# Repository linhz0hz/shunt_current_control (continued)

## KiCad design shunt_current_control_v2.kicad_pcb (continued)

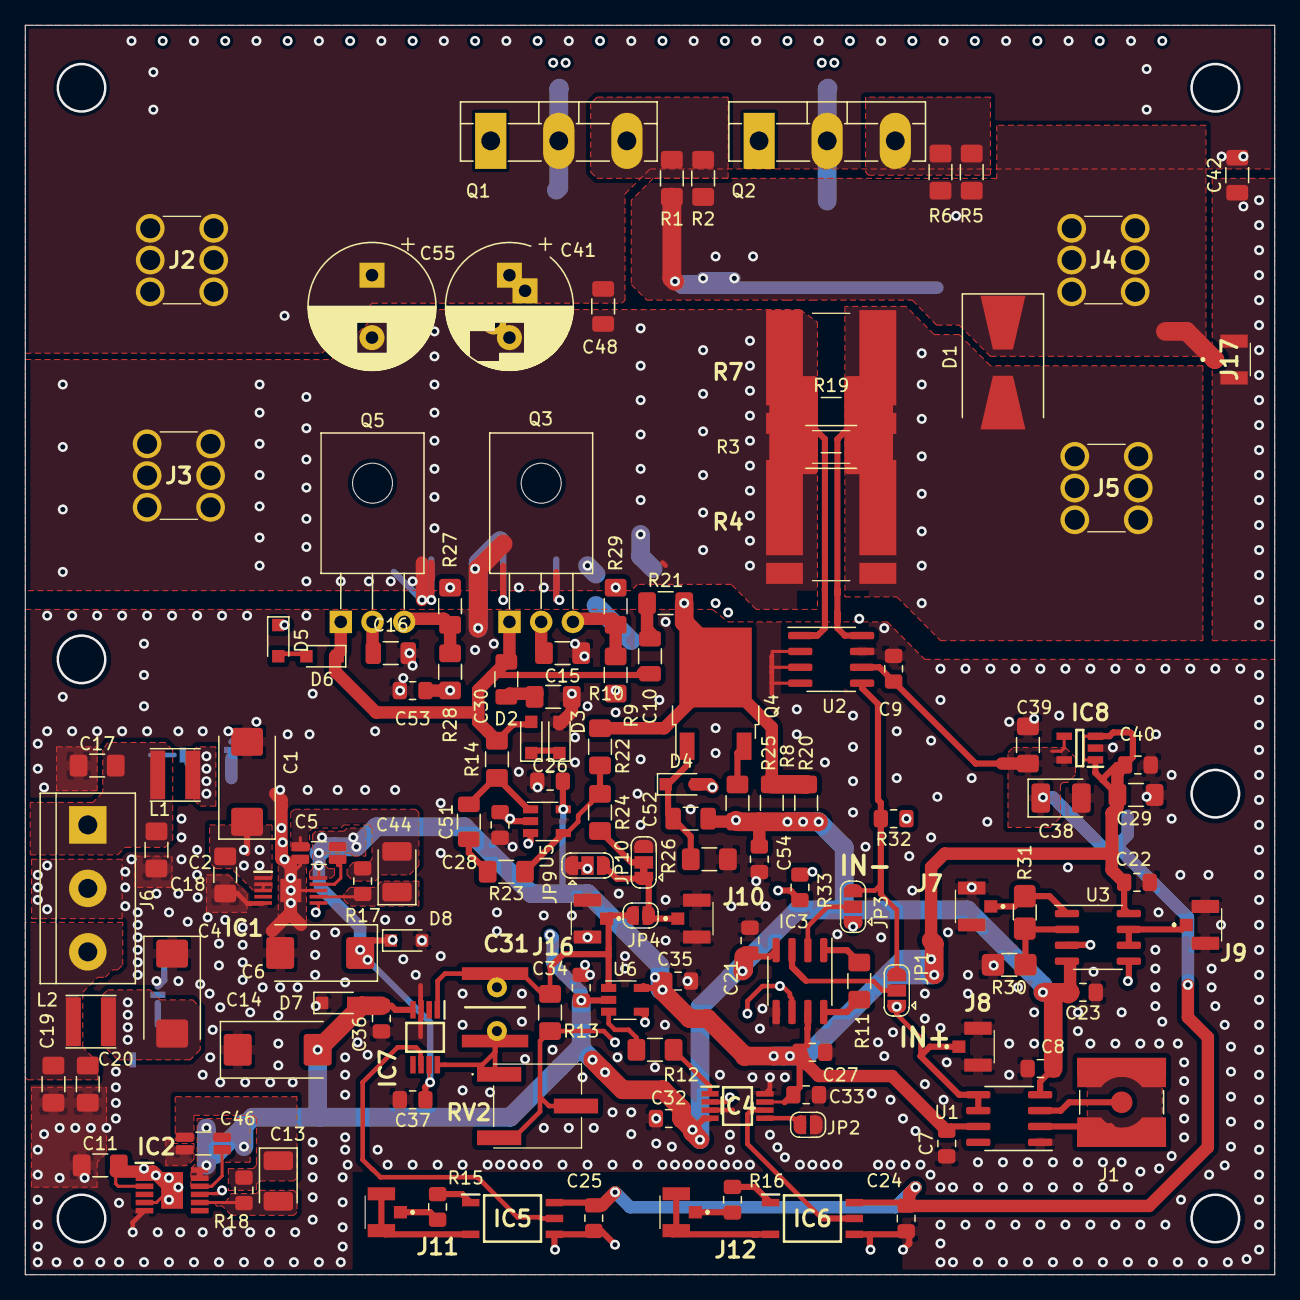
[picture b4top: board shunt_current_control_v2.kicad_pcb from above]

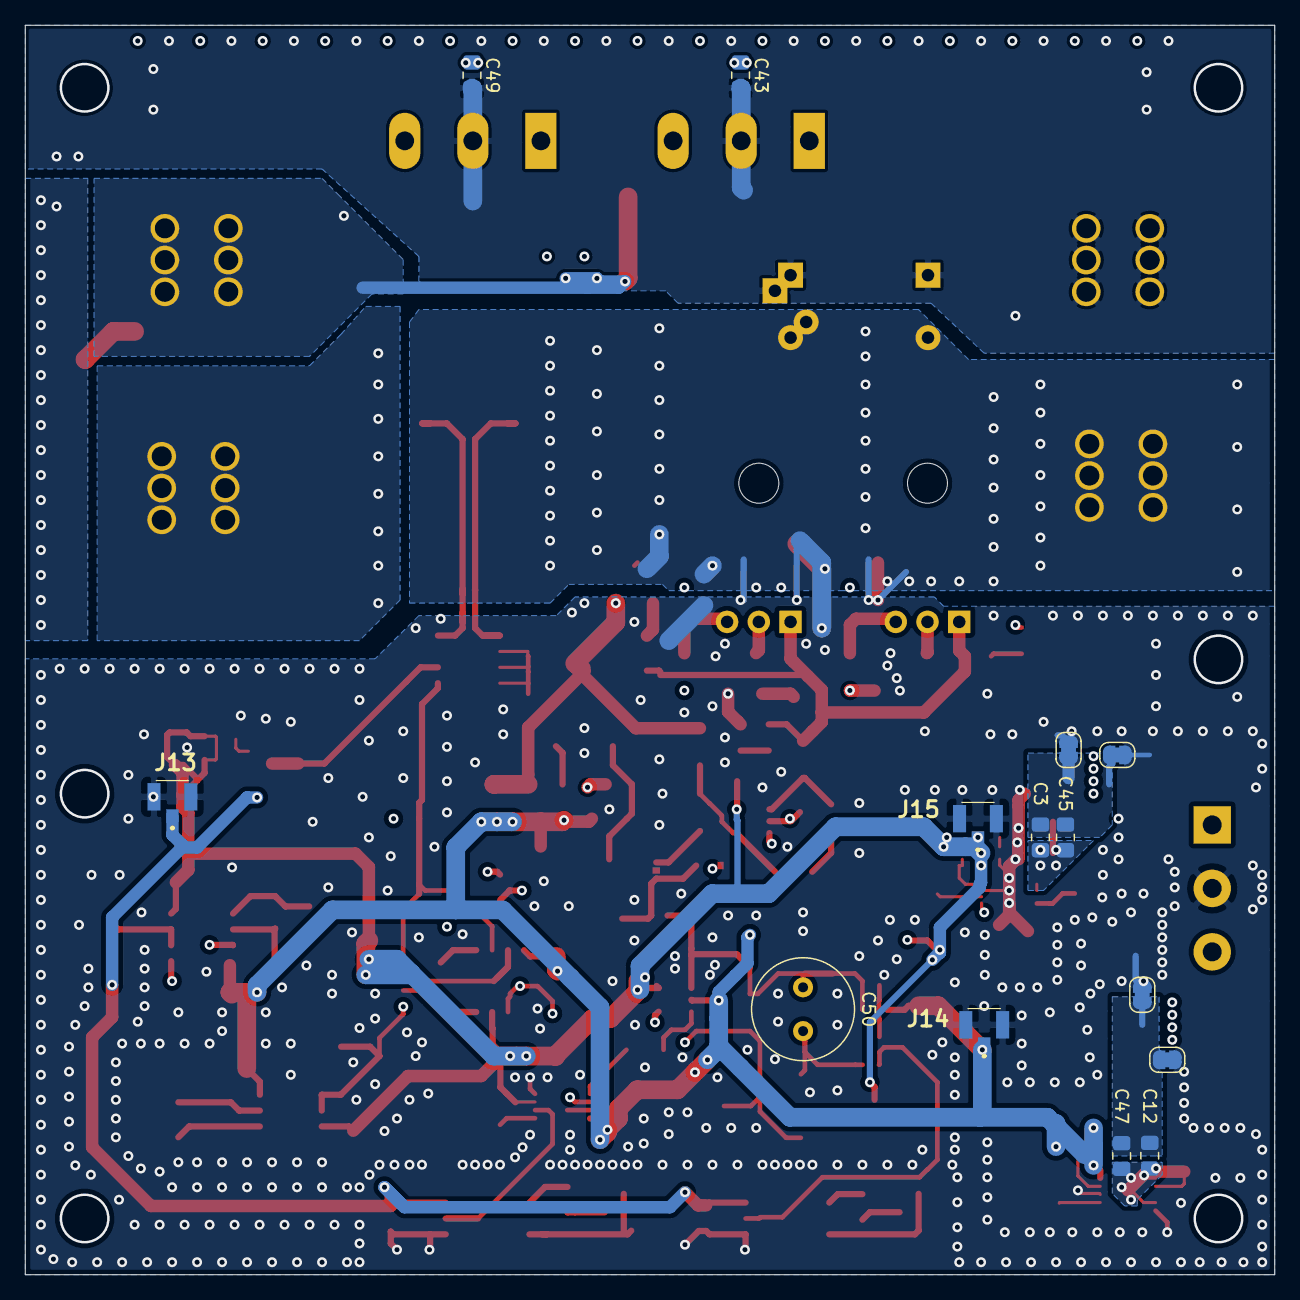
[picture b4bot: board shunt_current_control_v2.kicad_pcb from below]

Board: 4 copper layers, 100.0 x 100.0 mm, 144 parts (14 on the bottom side), 65 nets.

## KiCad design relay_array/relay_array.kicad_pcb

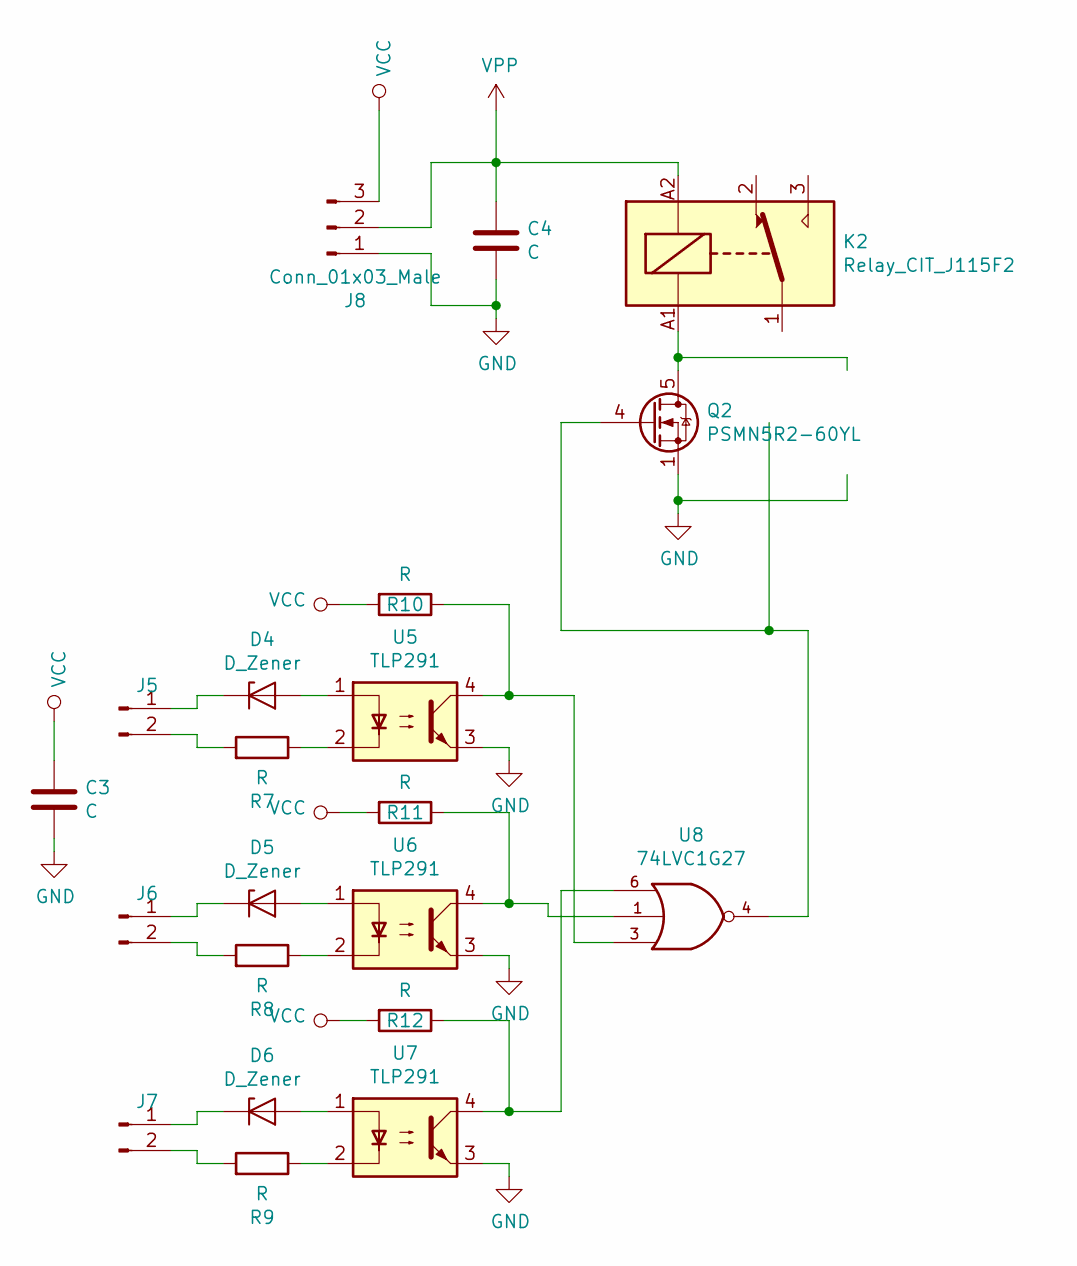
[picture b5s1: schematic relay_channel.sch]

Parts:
C1, C2: C; C_1206_3216Metric_Pad1.42x1.75mm_HandSolder
D1, D2, D3: D_Zener; D_SOD-323_HandSoldering
J1, J2, J3: Conn_01x02_Male; PinHeader_1x02_P2.54mm_Vertical
J4: Conn_01x03_Male; PinHeader_1x03_P2.54mm_Vertical
K1: Relay_CIT_J115F2
Q1: PSMN5R2-60YL; LFPAK56
R1, R2, R3, R4, R5, R6: R; R_0805_2012Metric_Pad1.15x1.40mm_HandSolder
U1, U2, U3: TLP291; SO-4_4.4x3.6mm_P2.54mm
U4: 74LVC1G27; TSOP-6_1.65x3.05mm_P0.95mm

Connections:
GND: C1.2, C2.2, J4.1, Q1.1 (S), Q1.2 (S), Q1.3 (S), U1.3, U2.3, U3.3, U4.2 (GND); also elsewhere on the board
unnamed: D1.1 (K), J1.1
unnamed: D1.2 (A), U1.1
unnamed: D2.1 (K), J2.1
unnamed: D2.2 (A), U2.1
unnamed: D3.1 (K), J3.1
unnamed: D3.2 (A), U3.1
unnamed: J1.2, R1.2
unnamed: J2.2, R2.2
unnamed: J3.2, R3.2
unnamed: K1.A1, Q1.5 (D)
unnamed: Q1.4 (G), U4.4
unnamed: R1.1, U1.2
unnamed: R2.1, U2.2
unnamed: R3.1, U3.2
unnamed: R4.1, U1.4, U4.3
unnamed: R5.1, U2.4, U4.1
unnamed: R6.1, U3.4, U4.6
VCC: C2.1, J4.3, R4.2, R5.2, R6.2, U4.5 (VCC); also elsewhere on the board
VPP: C1.1, J4.2, K1.A2; also elsewhere on the board

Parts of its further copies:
C3, C4, C5, C6: C; C_1206_3216Metric_Pad1.42x1.75mm_HandSolder
D4, D5, D6, D7, D8, D9: D_Zener; D_SOD-323_HandSoldering
J5, J6, J7, J9, J10, J11: Conn_01x02_Male; PinHeader_1x02_P2.54mm_Vertical
J8, J12: Conn_01x03_Male; PinHeader_1x03_P2.54mm_Vertical
K2, K3: Relay_CIT_J115F2
Q2, Q3: PSMN5R2-60YL; LFPAK56
R7, R8, R9, R10, R11, R12, R13, R14, R15, R16, R17, R18: R; R_0805_2012Metric_Pad1.15x1.40mm_HandSolder
U5, U6, U7, U9, U10, U11: TLP291; SO-4_4.4x3.6mm_P2.54mm
U8, U12: 74LVC1G27; TSOP-6_1.65x3.05mm_P0.95mm

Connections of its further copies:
GND: C3.2, C4.2, C5.2, C6.2, J8.1, J12.1, Q2.1 (S), Q2.2 (S), Q2.3 (S), Q3.1 (S), Q3.2 (S), Q3.3 (S), U5.3, U6.3, U7.3, U8.2 (GND), U9.3, U10.3, U11.3, U12.2 (GND); also elsewhere on the board
unnamed: D4.1 (K), J5.1
unnamed: D4.2 (A), U5.1
unnamed: D5.1 (K), J6.1
unnamed: D5.2 (A), U6.1
unnamed: D6.1 (K), J7.1
unnamed: D6.2 (A), U7.1
unnamed: D7.1 (K), J9.1
unnamed: D7.2 (A), U9.1
unnamed: D8.1 (K), J10.1
unnamed: D8.2 (A), U10.1
unnamed: D9.1 (K), J11.1
unnamed: D9.2 (A), U11.1
unnamed: J5.2, R7.2
unnamed: J6.2, R8.2
unnamed: J7.2, R9.2
unnamed: J9.2, R13.2
unnamed: J10.2, R14.2
unnamed: J11.2, R15.2
unnamed: K2.A1, Q2.5 (D)
unnamed: K3.A1, Q3.5 (D)
unnamed: Q2.4 (G), U8.4
unnamed: Q3.4 (G), U12.4
unnamed: R7.1, U5.2
unnamed: R8.1, U6.2
unnamed: R9.1, U7.2
unnamed: R10.1, U5.4, U8.3
unnamed: R11.1, U6.4, U8.1
unnamed: R12.1, U7.4, U8.6
unnamed: R13.1, U9.2
unnamed: R14.1, U10.2
unnamed: R15.1, U11.2
unnamed: R16.1, U9.4, U12.3
unnamed: R17.1, U10.4, U12.1
unnamed: R18.1, U11.4, U12.6
VCC: C3.1, C5.1, J8.3, J12.3, R10.2, R11.2, R12.2, R16.2, R17.2, R18.2, U8.5 (VCC), U12.5 (VCC); also elsewhere on the board
VPP: C4.1, C6.1, J8.2, J12.2, K2.A2, K3.A2; also elsewhere on the board

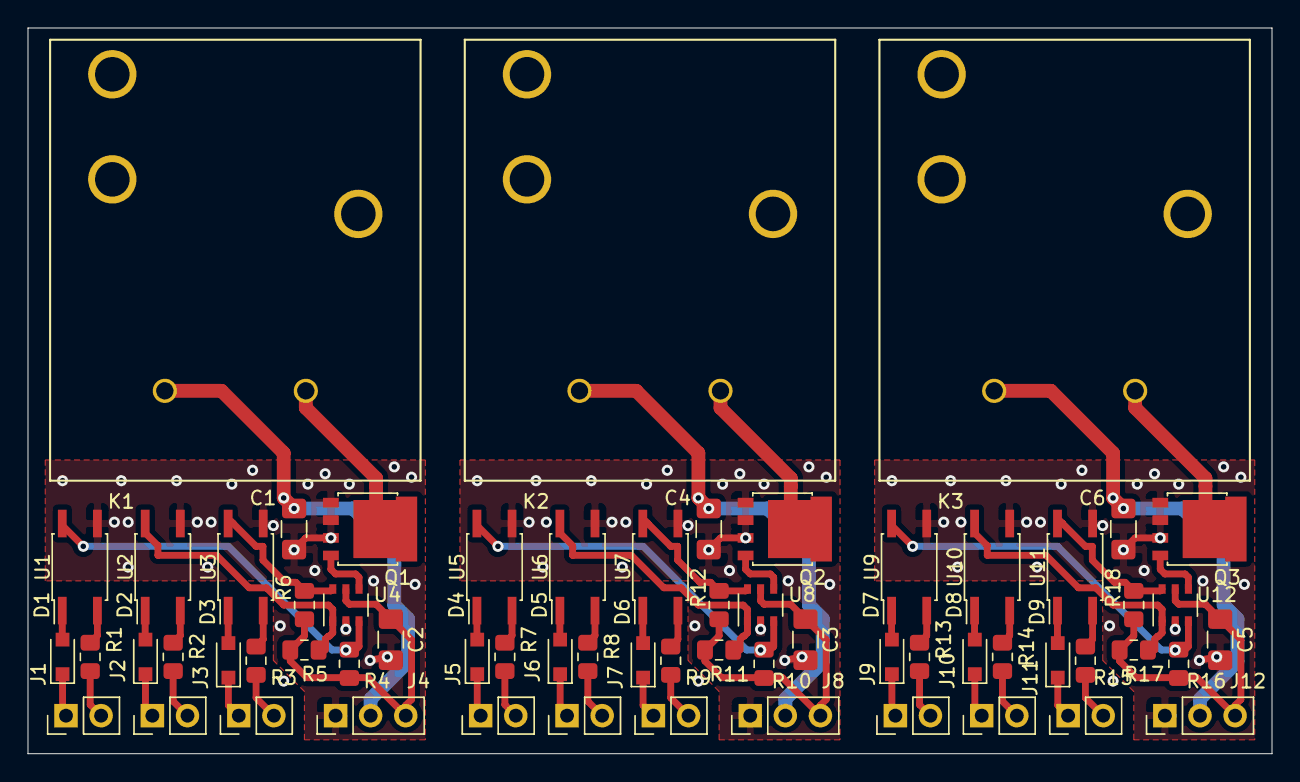
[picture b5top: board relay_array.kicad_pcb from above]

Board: 2 copper layers, 90.0 x 52.5 mm, 63 parts (0 on the bottom side), 54 nets.

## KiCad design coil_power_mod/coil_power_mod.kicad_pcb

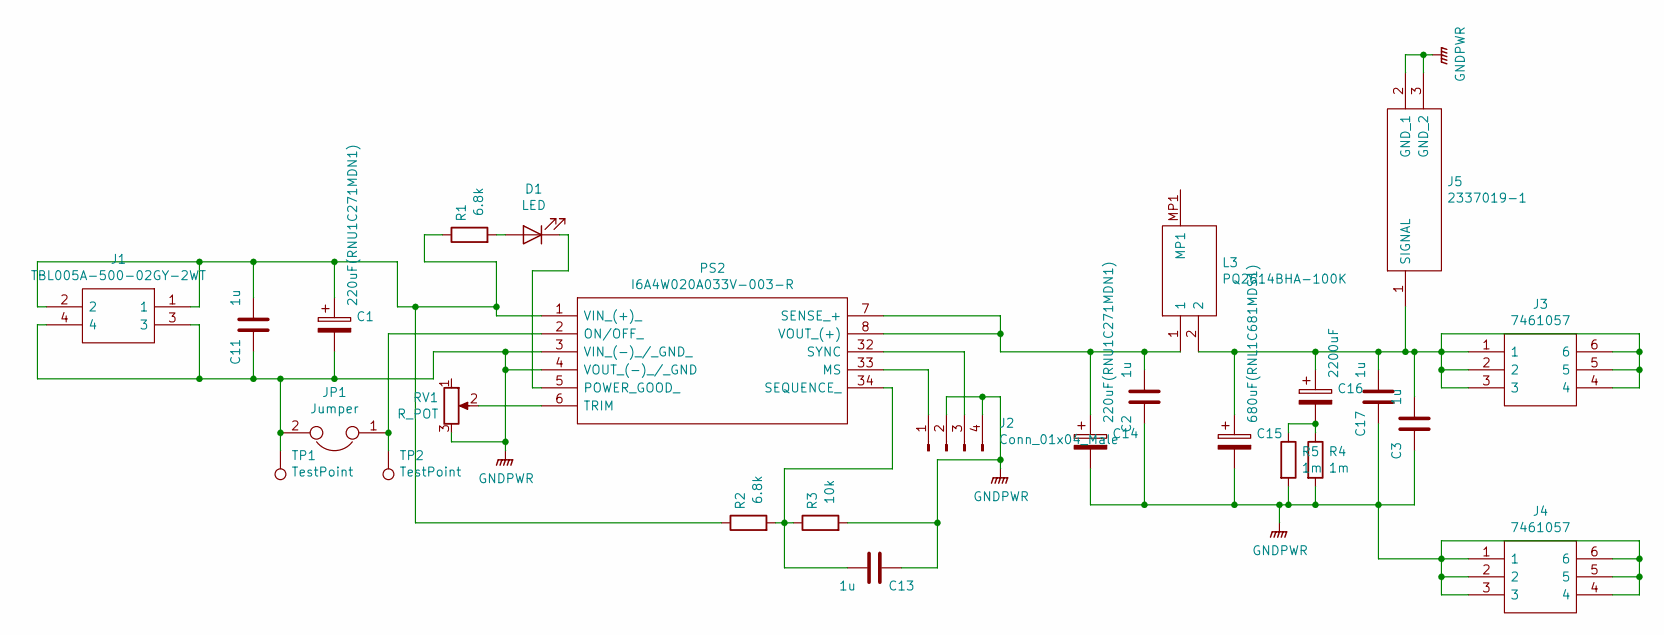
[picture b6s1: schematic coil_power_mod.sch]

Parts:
C1, C14: 220uF(RNU1C271MDN1); CP_Radial_D8.0mm_P3.50mm
C2, C3, C11, C13: 1u; C_1206_3216Metric_Pad1.42x1.75mm_HandSolder
C15: 680uF(RNL1C681MDS1); CP_Radial_D8.0mm_P3.50mm
C16: 2200uF; CP_Radial_D10.0mm_P5.00mm_P7.50mm
C17: 1u; C_0805_2012Metric_Pad1.15x1.40mm_HandSolder
D1: LED; LED_1206_3216Metric_Pad1.42x1.75mm_HandSolder
J1: TBL005A-500-02GY-2WT; SHDR4W75P500_2X2_1100X1583X1630P; Mouser Part Number 490-TBL05A50002GY2WT
J2: Conn_01x04_Male; PinHeader_1x04_P2.54mm_Vertical
J3, J4: 7461057; Mouser Part Number 710-7461057
J5: 2337019-1; 23370191; Mouser Part Number 571-2337019-1
JP1: Jumper; SolderJumper-2_P1.3mm_Bridged_RoundedPad1.0x1.5mm
L3: PQ2614BHA-100K; PQ2614BLA1R0K; Mouser Part Number 652-PQ2614BHA-100K
PS2: I6A4W020A033V-003-R; I6A4W020A033V003R; Mouser Part Number 967-I6A4W020A033V003
R1, R2: 6.8k; R_Axial_DIN0204_L3.6mm_D1.6mm_P5.08mm_Horizontal
R3: 10k; R_Axial_DIN0204_L3.6mm_D1.6mm_P5.08mm_Horizontal
R4: 1m; R_2512_6332Metric_Pad1.52x3.35mm_HandSolder
R5: 1m; R_Axial_DIN0204_L3.6mm_D1.6mm_P5.08mm_Horizontal
RV1: R_POT; 3361P1253GLF
TP1, TP2: TestPoint; TestPoint_Loop_D1.80mm_Drill1.0mm_Beaded

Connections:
GNDPWR: C1.2, C2.2, C3.2, C11.2, C13.2, C14.2, C15.2, C17.2, J1.3, J1.4, J2.2, J2.4, J4.1, J4.2, J4.3, J4.4, J4.5, J4.6, J5.2 (GND_1), J5.3 (GND_2), JP1.2, PS2.3 (VIN_(-)_/_GND_), PS2.4 (VOUT_(-)_/_GND), R3.2, R4.2, R5.2, RV1.3, TP1.1
unnamed: C1.1, C11.1, J1.1, J1.2, PS2.1 (VIN_(+)_), R1.1, R2.1
unnamed: C13.1, PS2.34 (SEQUENCE_), R2.2, R3.1
unnamed: C2.1, C14.1, L3.1, PS2.7 (SENSE_+), PS2.8 (VOUT_(+))
unnamed: C3.1, C15.1, C16.1, C17.1, J3.1, J3.2, J3.3, J3.4, J3.5, J3.6, J5.1 (SIGNAL), L3.2
unnamed: C16.2, R4.1, R5.1
unnamed: D1.1 (K), PS2.5 (POWER_GOOD_)
unnamed: D1.2 (A), R1.2
unnamed: J2.1, PS2.33 (MS)
unnamed: J2.3, PS2.32 (SYNC)
unnamed: JP1.1, PS2.2 (ON/OFF_), TP2.1
unnamed: PS2.6 (TRIM), RV1.2

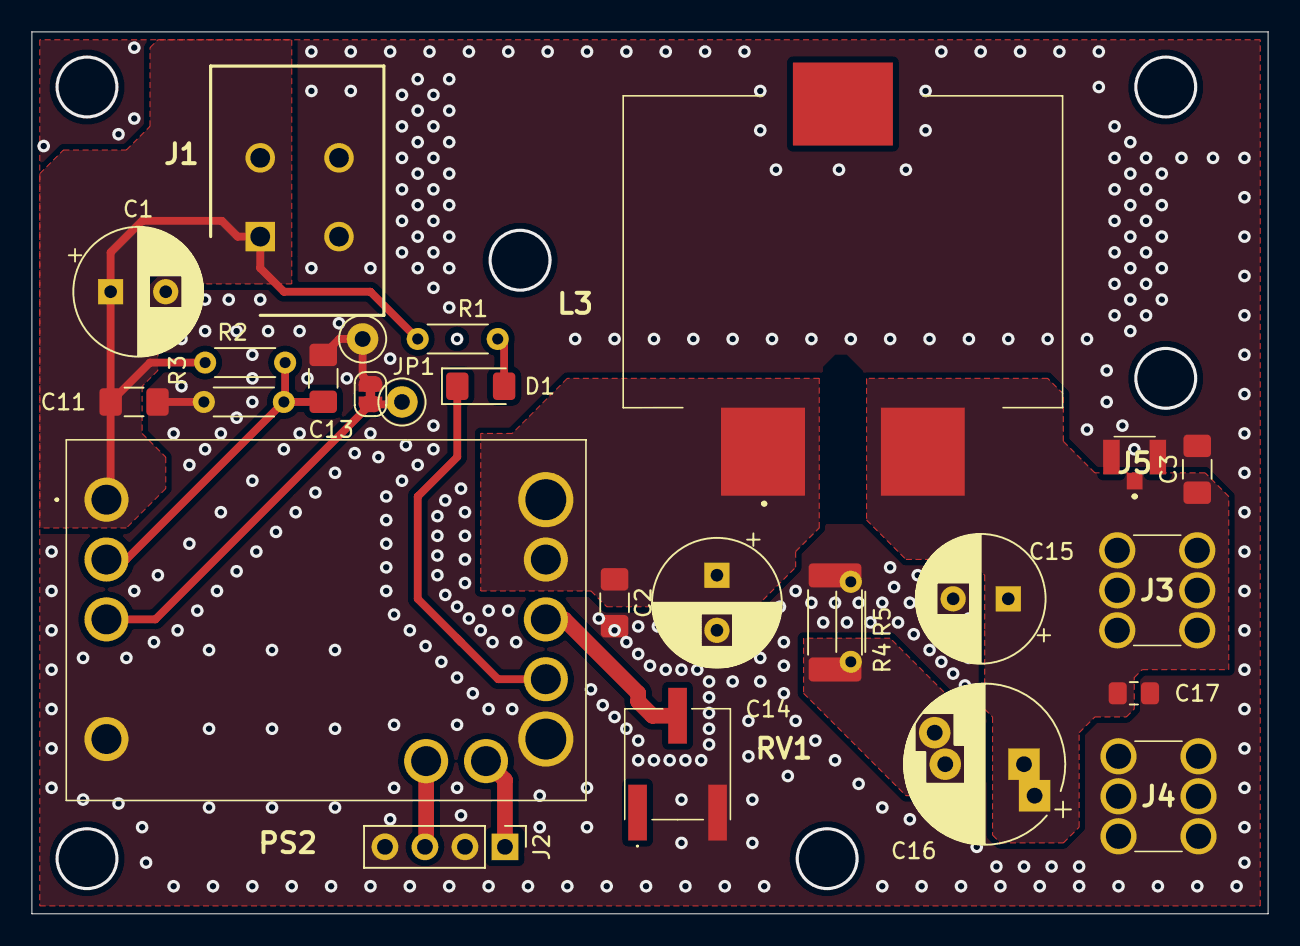
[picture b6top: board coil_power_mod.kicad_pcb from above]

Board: 2 copper layers, 78.5 x 56.0 mm, 26 parts (0 on the bottom side), 12 nets.

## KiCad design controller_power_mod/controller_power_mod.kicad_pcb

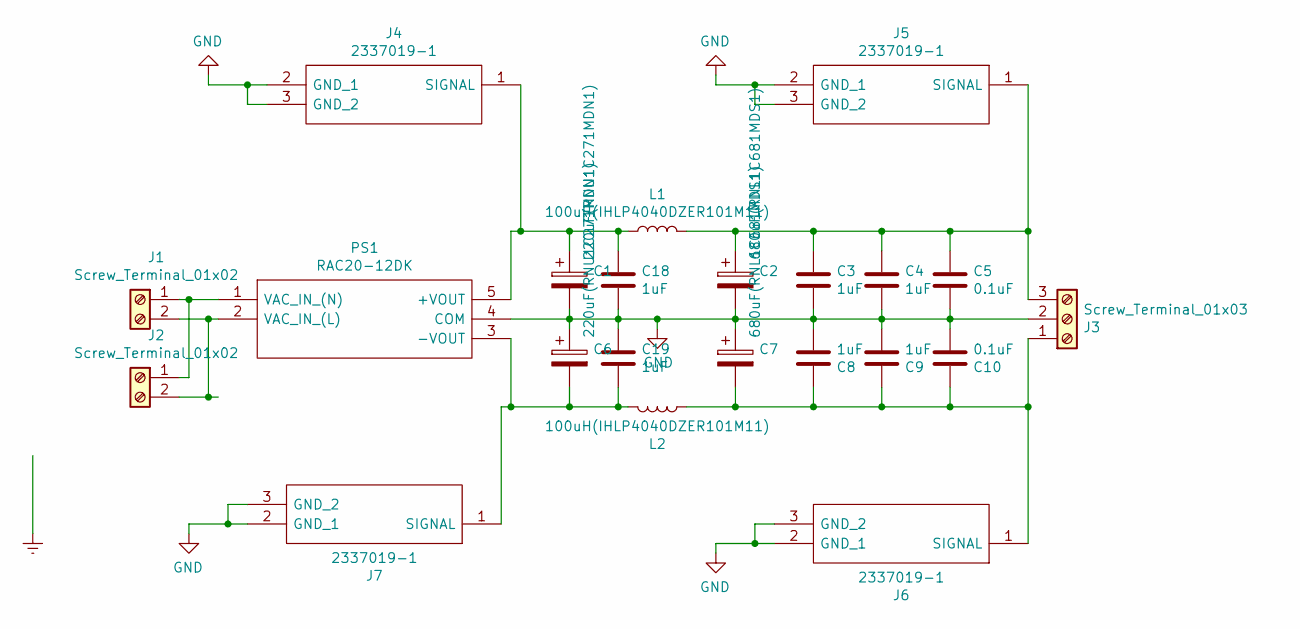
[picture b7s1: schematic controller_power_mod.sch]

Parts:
C1, C6: 220uF(RNU1C271MDN1); CP_Radial_D8.0mm_P3.50mm
C2, C7: 680uF(RNL1C681MDS1); CP_Radial_D8.0mm_P3.50mm
C3, C4, C8, C9, C18, C19: 1uF; C_1206_3216Metric_Pad1.42x1.75mm_HandSolder
C5, C10: 0.1uF; C_0805_2012Metric_Pad1.15x1.40mm_HandSolder
J1, J2: Screw_Terminal_01x02; TerminalBlock_bornier-2_P5.08mm
J3: Screw_Terminal_01x03; TerminalBlock_bornier-3_P5.08mm
J4, J5, J6, J7: 2337019-1; 23370191; Mouser Part Number 571-2337019-1
L1, L2: 100uH(IHLP4040DZER101M11); L_10.4x10.4_H4.8
PS1: RAC20-12DK; RAC2024SK; Mouser Part Number 919-RAC20-12DK

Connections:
GND: C1.2, C2.2, C3.2, C4.2, C5.2, C6.1, C7.1, C8.2, C9.2, C10.2, C18.2, C19.1, J3.2, J4.2 (GND_1), J4.3 (GND_2), J5.2 (GND_1), J5.3 (GND_2), J6.2 (GND_1), J6.3 (GND_2), J7.2 (GND_1), J7.3 (GND_2), PS1.4 (COM)
unnamed: C1.1, C18.1, J4.1 (SIGNAL), L1.1, PS1.5 (+VOUT)
unnamed: C2.1, C3.1, C4.1, C5.1, J3.3, J5.1 (SIGNAL), L1.2
unnamed: C7.2, C8.1, C9.1, C10.1, J3.1, J6.1 (SIGNAL), L2.2
unnamed: C6.2, C19.2, J7.1 (SIGNAL), L2.1, PS1.3 (-VOUT)
unnamed: J1.1, J2.1, PS1.1 (VAC_IN_(N))
unnamed: J1.2, J2.2, PS1.2 (VAC_IN_(L))

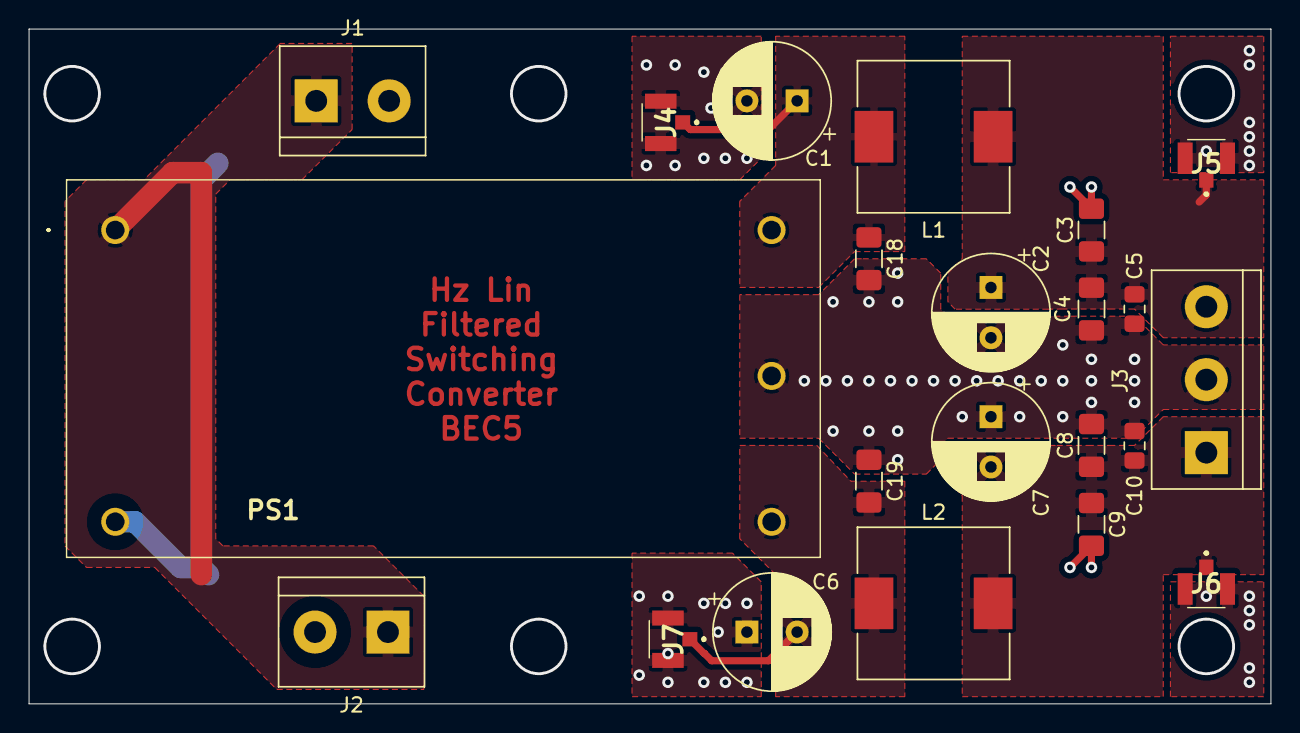
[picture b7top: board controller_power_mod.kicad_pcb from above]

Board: 2 copper layers, 86.5 x 47.0 mm, 22 parts (0 on the bottom side), 7 nets.

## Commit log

2021-09-03 First commit to store all previous work
2021-09-03 Updated design, to include proper feedback and a current bias. Note the sign of the feedback might still be problematic. Need to be checked again
2021-09-04 Allowed swapping feedback signs
2021-09-04 Design a common-mode choke / filter for the controller analog supplies. Avoid using one AC/DC converter for each board, but also suppress ground loops
2021-09-04 minor footprint adjustment to the choke/filter board
2021-09-05 Add a sub-board for lm317 regulators
2021-09-05 Fix library version mismatch
2021-09-05 migrate heirachycal sheets
2021-09-06 ground loop breaker temp progress
2021-09-06 ground loop breaker fin
2021-09-06 Relay array board; Last checkup; Gerberfile updates
